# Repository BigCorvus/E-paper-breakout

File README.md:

# E-paper-breakout
A small universal e-paper breakout board for 24pin FPC EPD modules based on a standard schematic. Includes casellations for easy integration and a high side switch for complete power disconnect otion.

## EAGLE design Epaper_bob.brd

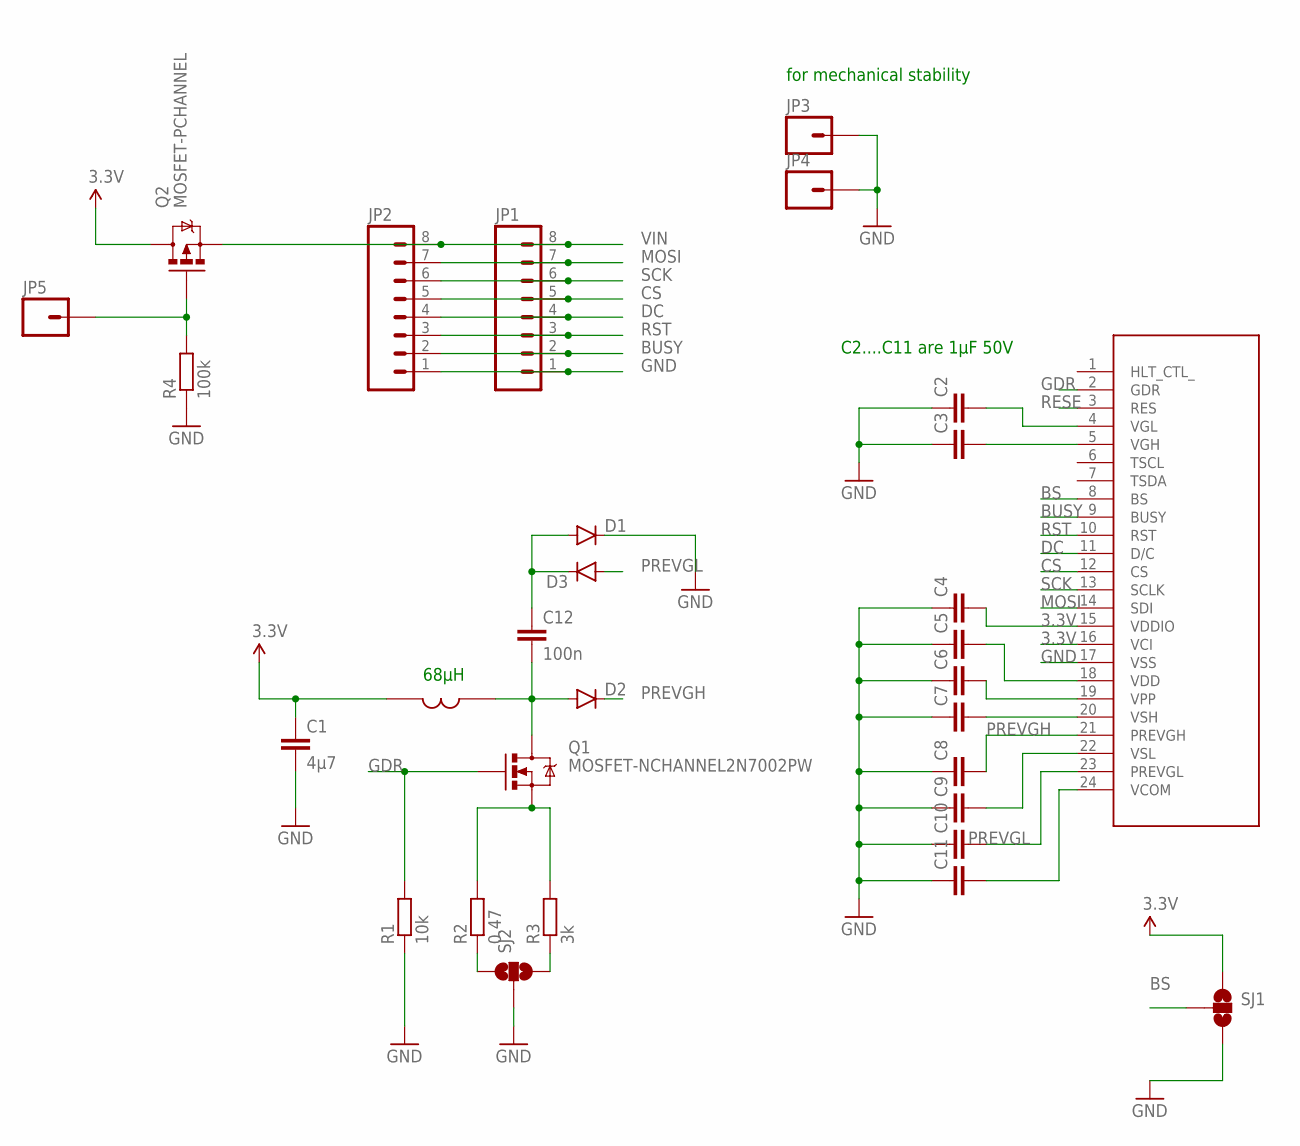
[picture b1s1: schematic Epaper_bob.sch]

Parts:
C1: 4µ7; C0603
C2, C3, C4, C5, C6, C7, C8, C9, C10, C11: C-EUC0603; C0603
C12: 100n; C0603
D1, D2, D3: DIODESOD123; SOD-123
JP1: M08NO_SILK; 1X08_PIN1_NO_SILK
JP2: M08; 1X08_ROUND
JP3, JP4, JP5: M01PTH_NO_SILK_YES_STOP; 1X01_NO_SILK
Q1: MOSFET-NCHANNEL2N7002PW; SOT323
Q2: MOSFET-PCHANNEL; SOT23-3
R1: 10k; R0603
R2: 0.47; R0603
R3: 3k; R0603
R4: 100k; R0603
SJ1, SJ2: SOLDERJUMPER_2WAYS; SJ_3
U$1: E-PAPER; FPC24
U$2: LQH3_INDUCTOR

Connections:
3.3V: C1.1, C4.2, Q2.3 (D), SJ1.1, U$1.15 (VDDIO), U$1.16 (VCI), U$2.P$1 (2)
BS: SJ1.2, U$1.8 (BS)
BUSY: JP1.2, JP2.2, U$1.9 (BUSY)
CS: JP1.5, JP2.5, U$1.12 (CS)
DC: JP1.4, JP2.4, U$1.11 (D/C)
GDR: Q1.1 (G), R1.2, U$1.2 (GDR)
GND: C1.2, C2.1, C3.1, C4.1, C5.1, C6.1, C7.1, C8.1, C9.1, C10.1, C11.1, D1.C, JP1.1, JP2.1, JP3.1, JP4.1, R1.1, R4.1, SJ1.3, SJ2.2, U$1.17 (VSS)
MOSI: JP1.7, JP2.7, U$1.14 (SDI)
unnamed: C11.2, U$1.24 (VCOM)
unnamed: C2.2, U$1.4 (VGL)
unnamed: C9.2, U$1.22 (VSL)
unnamed: C3.2, U$1.5 (VGH)
unnamed: C7.2, U$1.20 (VSH)
unnamed: C6.2, U$1.19 (VPP)
unnamed: C5.2, U$1.18 (VDD)
unnamed: R2.1, SJ2.1
unnamed: R3.1, SJ2.3
unnamed: Q1.2 (S), R2.2, R3.2
unnamed: JP5.1, Q2.1 (G), R4.2
unnamed: C12.2, D2.A, Q1.3 (D), U$2.P$2
unnamed: C12.1, D1.A, D3.C
PREVGH: C8.2, D2.C, U$1.21 (PREVGH)
PREVGL: C10.2, D3.A, U$1.23 (PREVGL)
RESE: U$1.3 (RES)
RST: JP1.3, JP2.3, U$1.10 (RST)
SCK: JP1.6, JP2.6, U$1.13 (SCLK)
VIN: JP1.8, JP2.8, Q2.2 (S)

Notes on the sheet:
C2....C11 are 1µF 50V
68µH
for mechanical stability

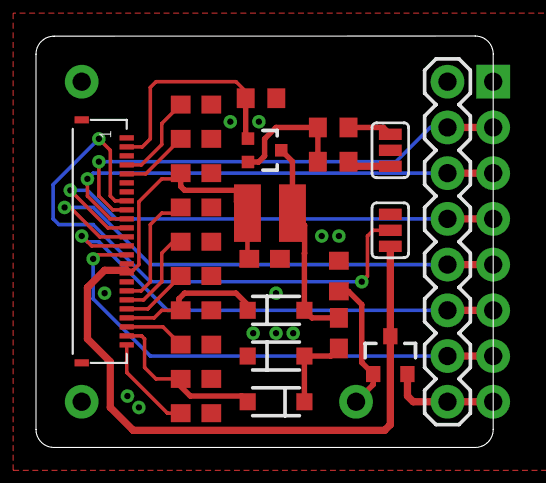
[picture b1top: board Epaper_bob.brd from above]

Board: 2 copper layers, 25.4 x 22.9 mm, 30 parts (0 on the bottom side), 26 nets.

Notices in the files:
parts and their libraries:
SparkFun-DiscreteSemi: Licensing: Creative Commons ShareAlike 4.0 International - https://creativecommons.org/licenses/by-sa/4.0
